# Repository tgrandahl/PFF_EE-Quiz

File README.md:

# PFF_EE-Quiz
EE-Quiz for PFF screening
Tyler Grandahl - July 27th 2017

The design files are provided in response to the following request:

Using KiCAD, design a circuit schematic for an analog amplifier with the following features:
-Uses a 5VDC power supply. Assumes the signal to be amplified shares the same ground as the power supply.
-Amplifies an input analog signal that can range from 0 to 2.0V so that the output ranges from 0 to 5V.
-Contains a bill of materials (BOM) specifying the chosen components and how to source them.
-Has an adjustable gain. And a low-pass filter with adjustable cut-off to filter-out noise from the input analog signal.
-OPTIONAL: Is implemented as a routed PCB.
 
The design can be submitted as a GitHub repository file containing the KiCAD project and a printable (Letter) PDF with the schematic and if available another PDF in 1:1 scale of the routed PCB.

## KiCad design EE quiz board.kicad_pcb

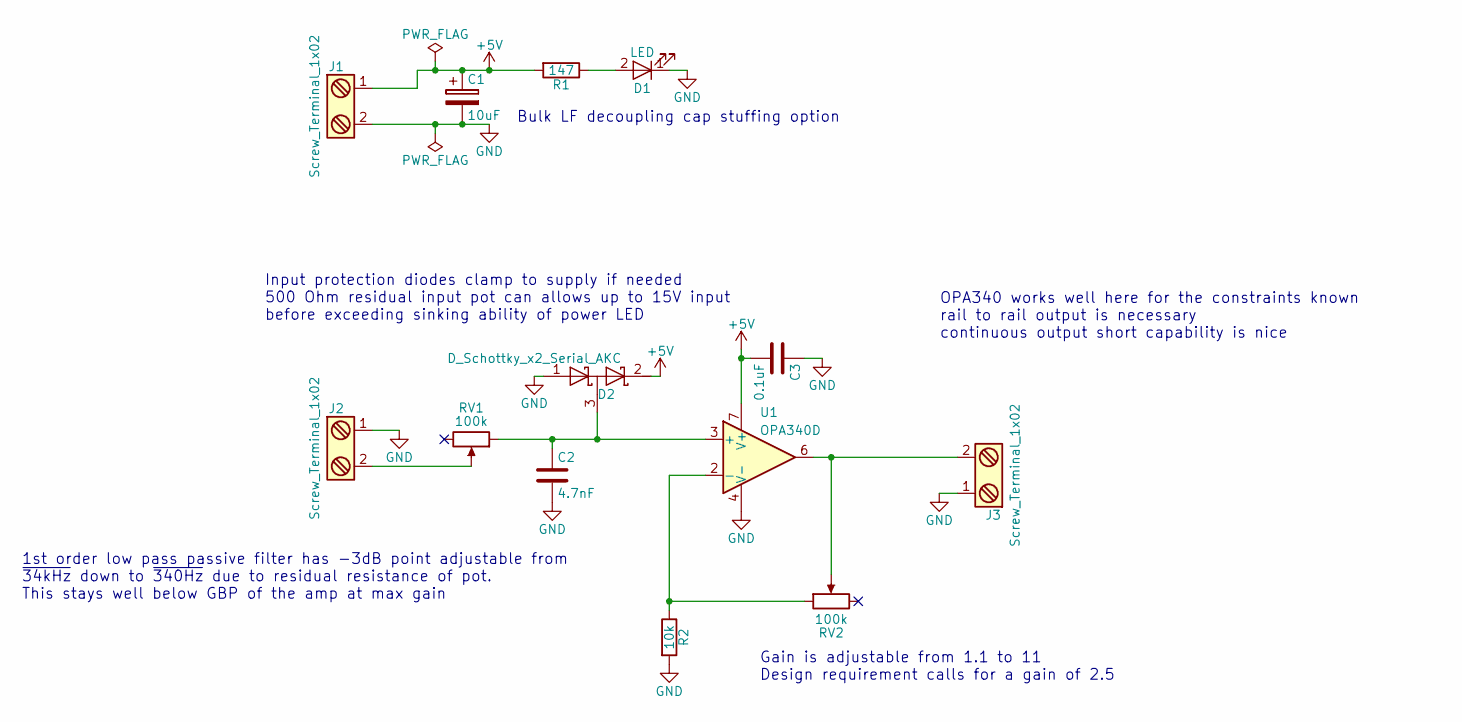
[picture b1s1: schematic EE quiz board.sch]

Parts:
C1: 10uF; CP_Tantalum_Case-A_EIA-3216-18_Hand; MFG PN T494A106K016AT
C2: 4.7nF; C_0603_HandSoldering; MFG PN C0603C472K4RACTU
C3: 0.1uF; C_0603_HandSoldering; MFG PN C0603C104K4RACTU
D1: LED; LED_0805_HandSoldering; MFG PN LTST-C171GKT
D2: D_Schottky_x2_Serial_AKC; SOT-23_Handsoldering; MFG PN SBAT54SLT1G
J1, J2, J3: Screw_Terminal_1x02; TerminalBlock_Pheonix_MKDS1.5-2pol; MFG PN 1868733
R1: 147; R_0603_HandSoldering; MFG PN ERJ-3EKF1470V
R2: 10k; R_0603_HandSoldering; MFG PN ERJ-PA3F1002V
RV1, RV2: 100k; Potentiometer_Bourns_PTV09A-1_Horizontal; MFG PN PTV09A-4025F-B104
U1: OPA340D; SOIC-8_3.9x4.9mm_Pitch1.27mm; MFG PN OPA340UA/2K5

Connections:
+5V: C1.1, C3.2, D2.2 (K), J1.1, R1.2, U1.7 (V+)
GND: C1.2, C2.2, C3.1, D1.1 (K), D2.1 (A), J1.2, J2.1, J3.1, R2.2, U1.4 (V-)
unnamed: C2.1, D2.3 (common), RV1.1, U1.3 (+)
unnamed: D1.2 (A), R1.1
unnamed: J2.2, RV1.2
unnamed: J3.2, RV2.2, U1.6
unnamed: R2.1, RV2.1, U1.2 (-)

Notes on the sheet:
Input protection diodes clamp to supply if needed 500 Ohm residual input pot can allows up to 15V input before exceeding sinking ability of power LED
OPA340 works well here for the constraints known rail to rail output is necessary continuous output short capability is nice
1st order low pass passive filter has -3dB point adjustable from ~34kHz down to ~340Hz due to residual resistance of pot. This stays well below GBP of the amp at max gain
Gain is adjustable from 1.1 to 11 Design requirement calls for a gain of 2.5
Bulk LF decoupling cap stuffing option

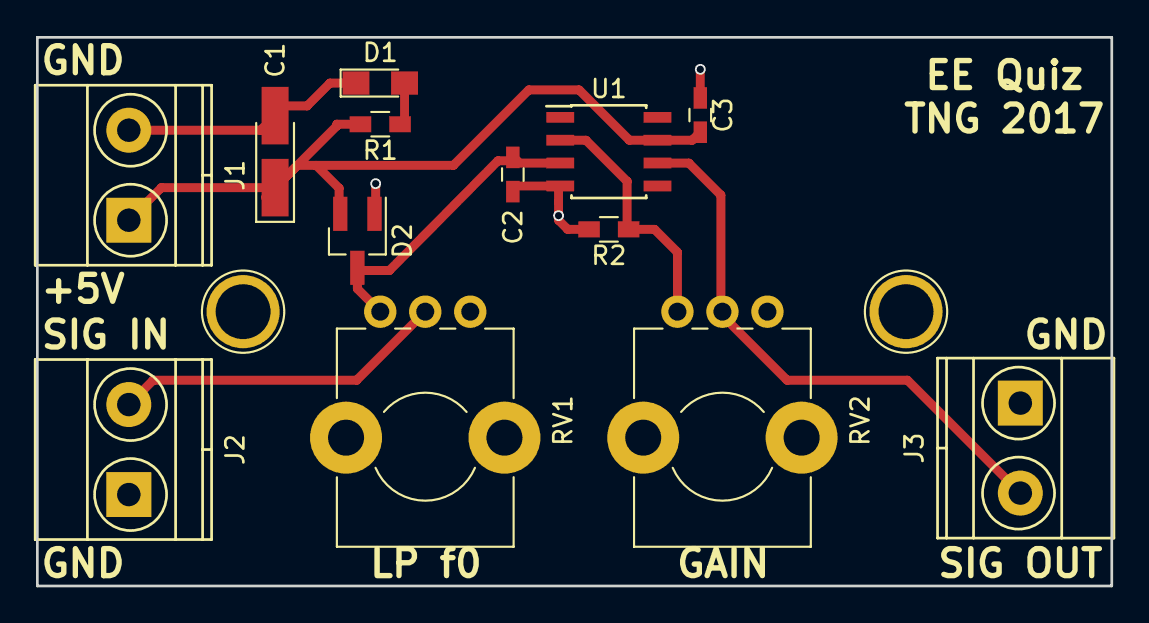
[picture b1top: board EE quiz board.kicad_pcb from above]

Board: 2 copper layers, 59.7 x 30.5 mm, 13 parts (0 on the bottom side), 7 nets.

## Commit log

2017-07-27 adding project description
2017-07-27 Add files via upload
    initial commit of KiCad design files
